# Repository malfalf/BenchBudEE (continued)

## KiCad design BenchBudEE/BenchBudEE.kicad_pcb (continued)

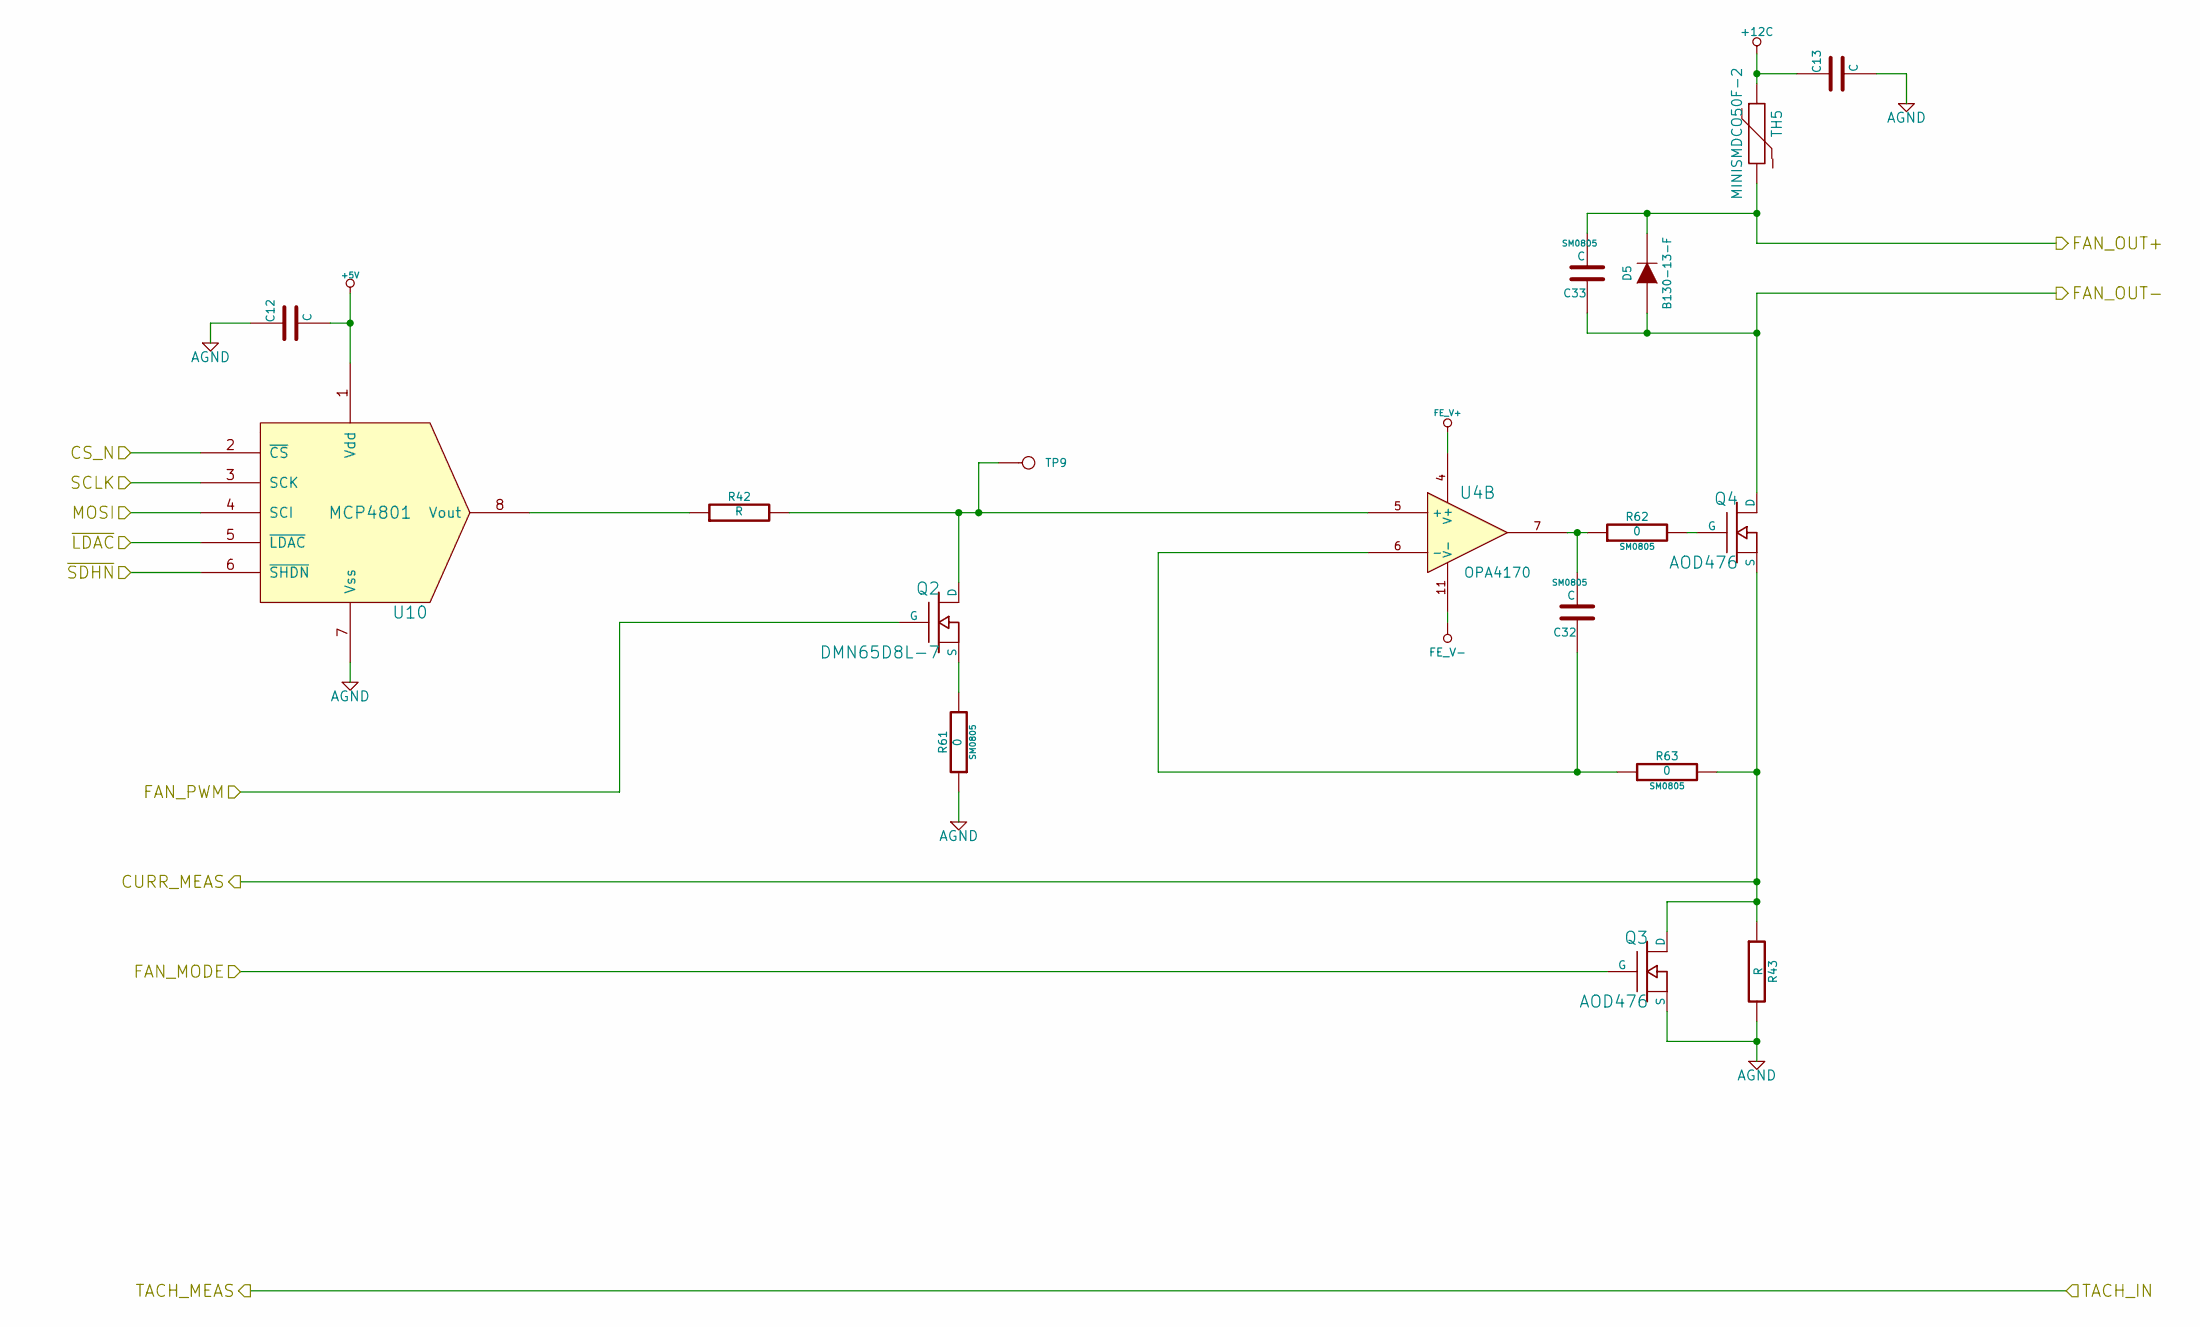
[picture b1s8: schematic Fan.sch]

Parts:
C12, C13: C
C32, C33: C; SM0805
D5: B130-13-F; MFG Part Number B130-13-F
Q2: DMN65D8L-7; MFG Part Number DMN65D8L-7
Q3, Q4: AOD476; MFG Part Number AOD476
R42, R43: R
R61, R62, R63: 0; SM0805
TH5: MINISMDCO50F-2; MFG Part Number MINISMDCO50F-2
TP9: DAC_OUT
U4: OPA4170
U10: MCP4801

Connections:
+5V: C12.2, U10.1 (Vdd); also elsewhere on the board
+12C: C13.1, TH5.1; also elsewhere on the board
/Arduino/CURR_MEAS: Q3.2 (D), Q4.3 (S), R43.1, R63.2; also elsewhere on the board
/Arduino/FAN_MODE: Q3.1 (G); also elsewhere on the board
/Arduino/FAN_PWM: Q2.G; also elsewhere on the board
/Arduino/MOSI: U10.4 (SCI); also elsewhere on the board
/Arduino/SCLK: U10.3 (SCK); also elsewhere on the board
/Arduino/~LDAC: U10.5 (~LDAC); also elsewhere on the board
/Fan/CS_N: U10.2 (~CS); also elsewhere on the board
/Fan/FAN_OUT+: C33.2, D5.2 (K), TH5.2; also elsewhere on the board
/Fan/FAN_OUT-: C33.1, D5.1 (A), Q4.2 (D); also elsewhere on the board
/Fan/~SDHN: U10.6 (~SHDN); also elsewhere on the board
AGND: C12.1, C13.2, Q3.3 (S), R43.2, R61.1, U10.7 (Vss); also elsewhere on the board
FE_V+: U4.4 (V+); also elsewhere on the board
FE_V-: U4.11 (V-); also elsewhere on the board
unnamed: R42.1, U10.8 (Vout)
unnamed: Q4.1 (G), R62.2
unnamed: C32.1, R63.1, U4.6 (-)
unnamed: Q2.3 (S), Q2.S, R61.2
unnamed: C32.2, R62.1, U4.7
unnamed: Q2.2 (D), Q2.D, R42.2, TP9.1, U4.5 (+)

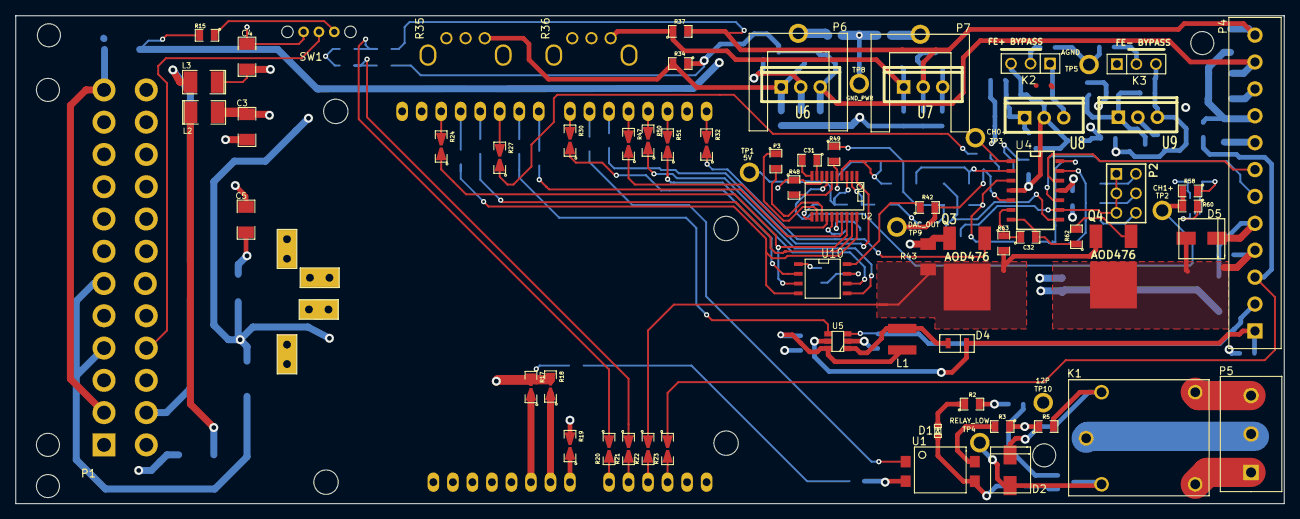
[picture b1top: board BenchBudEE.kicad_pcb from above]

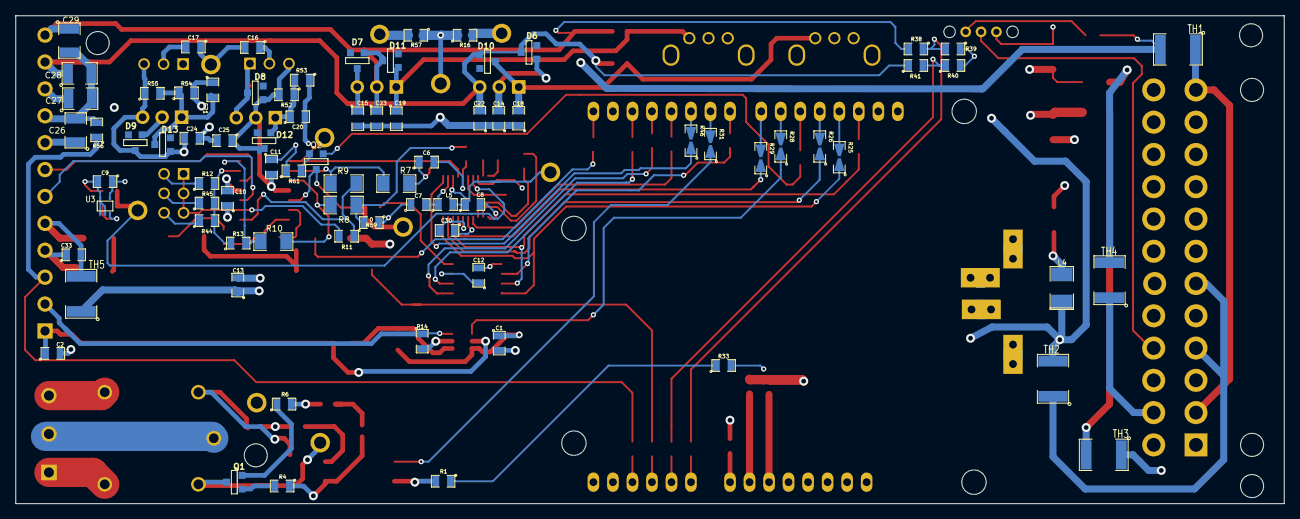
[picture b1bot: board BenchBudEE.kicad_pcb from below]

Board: 4 copper layers, 165.1 x 63.5 mm, 160 parts (79 on the bottom side), 114 nets.

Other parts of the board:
3 mm, 3 mm#2, 3 mm#3, 3 mm#4: VAL**; 3mm-NPTH

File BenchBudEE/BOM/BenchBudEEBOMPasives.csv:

Value;Quantity;RefDes;Footprint
1U;10;C1 C2 C7 C8 C9 C10 C11 C12 C13 C33;SM0805
100P;1;C6;SM0805
10U;8;C14 C15 C16 C17 C22 C23 C24 C25;SM0805
.01U;4;C18 C19 C20 C21;SM0805
NOPOP;5;C30 C31 C32 R16 R57;SM0805
10U;3;C3 C4 C5;SM1206
10U;4;C26 C27 C28 C29;SM1210
4.7U;1;L5;SM0805
0;13;R3 R5 R6 R15 R33 R42 R48 R49 R56 R59 R61 R62 R63;SM0805
0;20;R17 R18 R19 R20 R21 R22 R23 R24 R25 R26 R27 R28 R29 R30 R31 R32 R46 R47 R50 R51;SM0805-SB_2
1;1;R43;SM1206_NotOutline
10;1;R44;SM0805
15;1;R14;SM0805
100;2;R4 R45;SM0805
200;2;R1 R2;SM0805
715;2;R34 R37;SM0805
1000;1;R12;SM0805
1K;4;R39 R40 R58 R60;SM0805
1.3K;2;R53 R54;SM0805
3K;2;R38 R41;SM0805
5k;2;R35 R36;EVUE3K
5K;2;R11 R13;SM0805
5K;2;R7 R8;SM1206
9.1K;2;R52 R55;SM0805
200K;2;R9 R10;SM1206

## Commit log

2014-01-30 New KiCAD project
    Blank schematic and layout file.
2014-02-01 Block Diagram and hierarchy blocks created
2014-02-01 Inputs and Outputs added
2014-02-04 Thermocoupler Block diagram
2014-02-04 Fan driver block diagram
2014-02-08 Relay block diagram
    Relay block diagram and BenchBudEE library created
2014-02-08 Power Protection and filtering module added
2014-02-09 Power Control Conditioning and monitoring block diagram
2014-02-09 LED Driver block diagram
2014-02-09 Arduino block diagram
2014-02-11 Fan/current module refactoring
2014-02-16 PCB Outline created and changes during components choice
2014-02-17 Associating and Placing the Relay Module
2014-02-22 Associating and Placingthe Thermocouple Module
2014-02-22 Associating and Placing the Terminal Block Module
2014-02-22 Associating and Placing Arduino Block Module
2014-02-22 Associating and Placing Fan Module
2014-02-23 Associating and Placing the Power protection module
2014-02-23 Associating and Placing the Power Modification Module
2014-02-27 Associating and Placing the LED Driver Module
2014-02-27 Finalizing the system part placement
2014-03-01 Ground and Power Planes
2014-03-01 Ground and Power Planes (after saving)
2014-03-01 Reality Check
2014-03-01 Layout Work Session 1
2014-03-01 Layout Work Session 2
2014-03-02 Layout Work Session 4
2014-03-02 Layout Work Session 5
2014-03-03 Layout Work Session 6
2014-03-03 Layout Work Session 6 (II)
2014-03-04 Layout Work Session 7
2014-03-04 Connecting Ground Planes
2014-03-05 Layout Work Session 8
2014-03-05 Layout Work Session 9
2014-03-08 Layout Work Session 10
2014-03-13 Layout Work Session 11
2014-03-15 Layout Work Session 12
2014-03-16 Layout Work Session 13
2014-03-16 Layout Work Session 14
2014-03-17 Layout Work Session 15
2014-03-17 Layout Work Session 16
2014-03-18 Layout Work Session 17
2014-03-20 Layout Work Session 18
2014-03-26 Analog IO Cleanup/Additions
2014-03-27 Changes due to external DFM
    Changes in the drill size
2014-03-31 Final Changes
2014-04-27 Changes for the BOM and BOMs
